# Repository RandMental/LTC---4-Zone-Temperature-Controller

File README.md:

# Labfin Temperature Controller
* 4 indepenednt zones 
* Web server for OTA monitoring and customisation
* MQTT client for Home Assistant 
* SD card for config

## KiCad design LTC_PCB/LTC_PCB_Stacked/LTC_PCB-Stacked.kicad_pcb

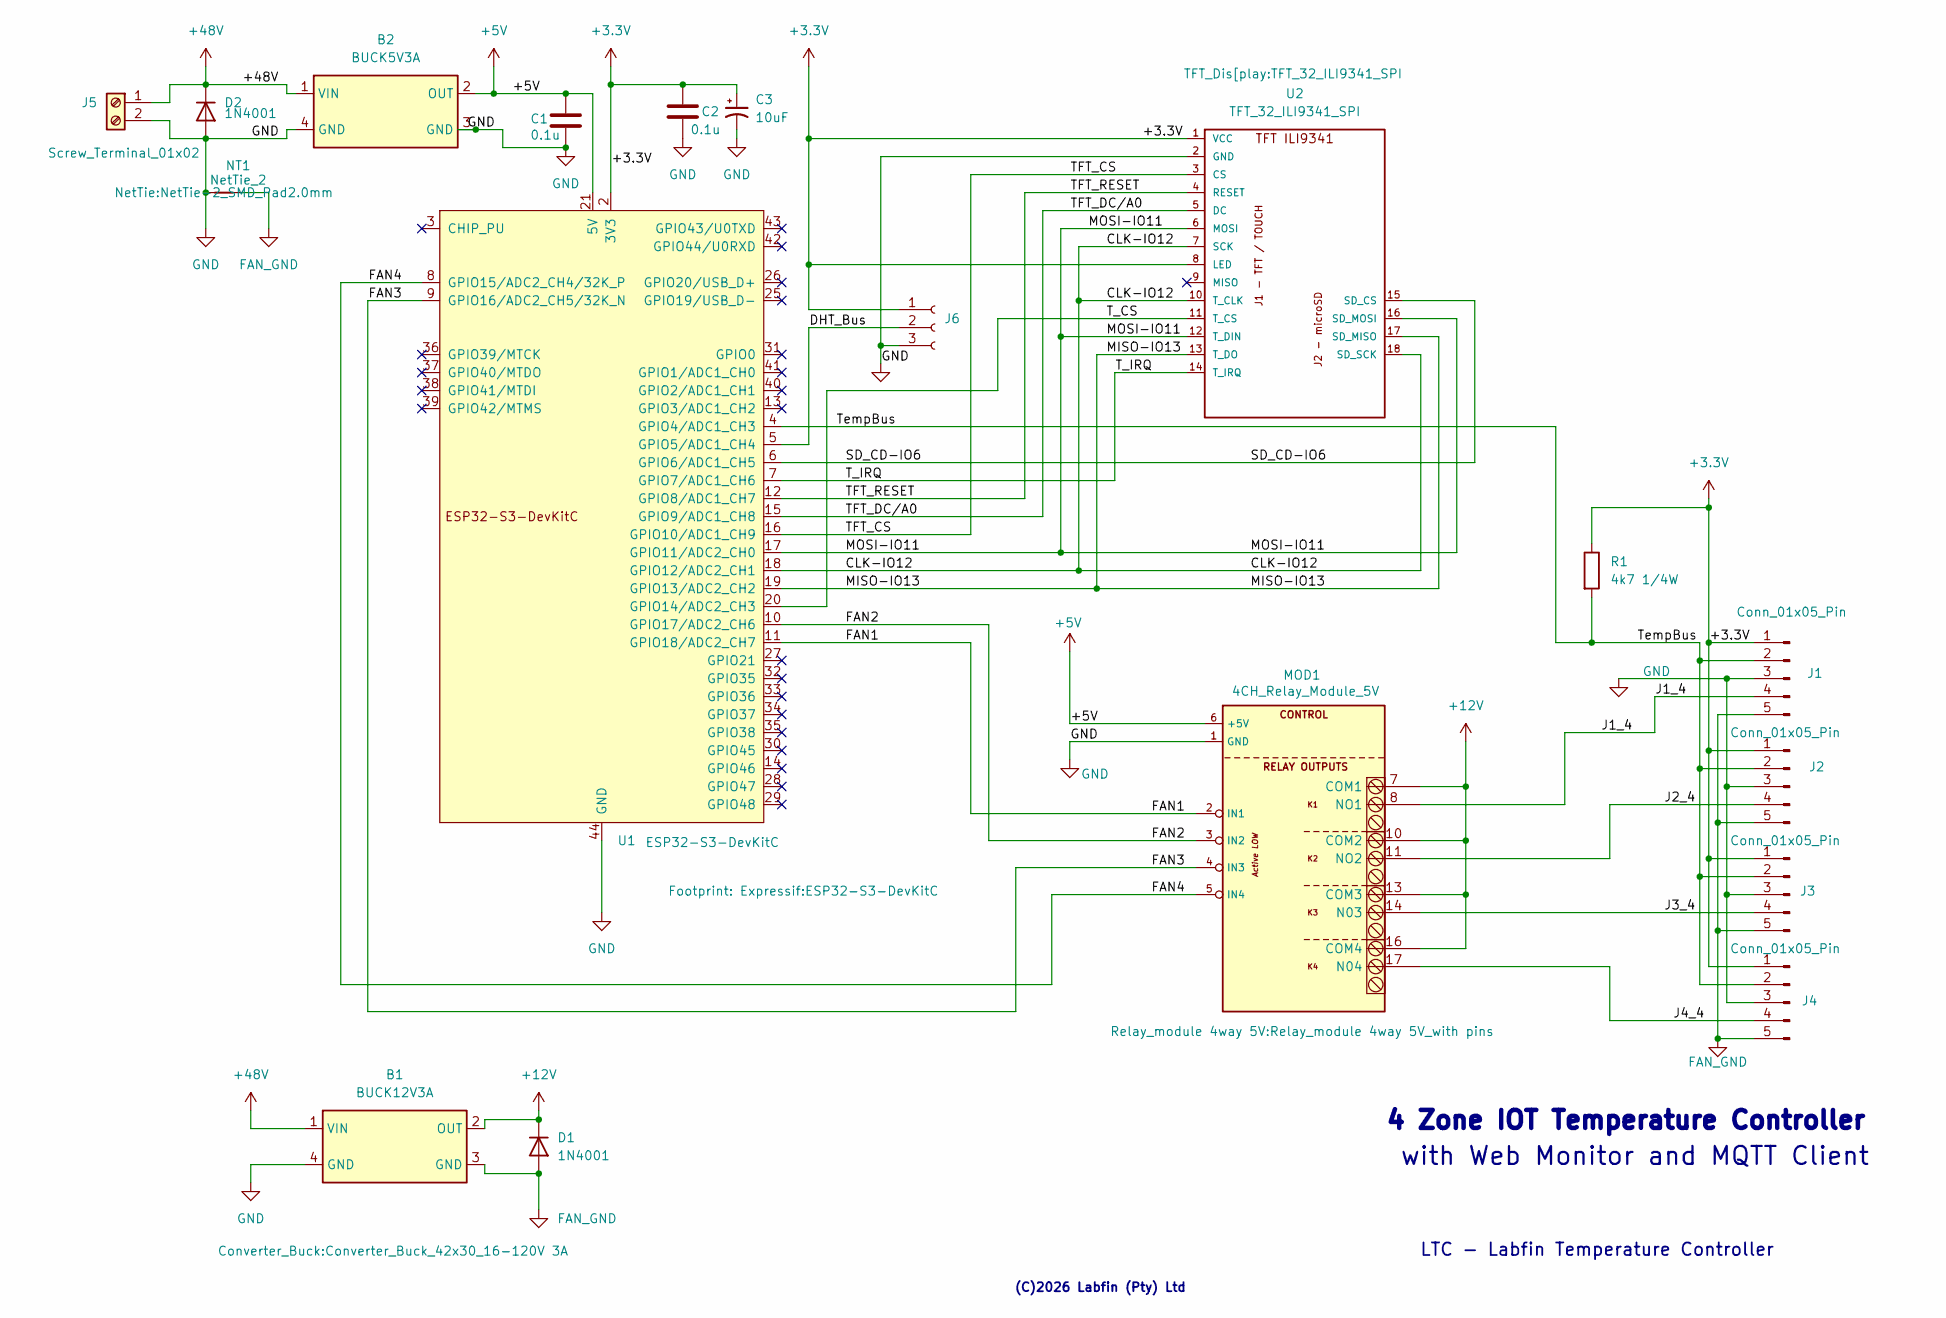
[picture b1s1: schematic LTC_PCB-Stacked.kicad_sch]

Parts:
B1: BUCK12V3A; Converter_Buck_42x30_16-120V 3A
B2: BUCK5V3A; Converter_Buck_42x30_16-120V 3A
C1, C2: 0.1u; C_Disc_D5.1mm_W3.2mm_P5.00mm
C3: 10uF; CP_Radial_D8.0mm_P5.00mm
D1, D2: 1N4001; D_DO-41_SOD81_P10.16mm_Horizontal
J1, J2, J3, J4: Conn_01x05_Pin; Molex_SL_171971-0005_1x05_P2.54mm_Vertical
J5: Screw_Terminal_01x02; Molex_KK-254_AE-6410-02A_1x02_P2.54mm_Vertical
J6: Conn_01x03_Socket; Molex_KK-254_AE-6410-03A_1x03_P2.54mm_Vertical
MOD1: 4CH_Relay_Module_5V; Relay_module 4way 5V_with pins; MPN SRD-05VDC-SL-C
NT1: NetTie_2; NetTie-2_SMD_Pad2.0mm
R1: 4k7 1/4W; R_Axial_DIN0207_L6.3mm_D2.5mm_P15.24mm_Horizontal
U1: ESP32-S3-DevKitC
U2: TFT_32_ILI9341_SPI

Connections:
+3.3V: C2.1, C3.1, J1.1, J2.1, J3.1, J4.1, J6.1, R1.1, U1.1 (3V3), U1.2 (3V3), U2.1 (VCC), U2.8 (LED)
+5V: B2.2 (OUT), C1.1, MOD1.6 (+5V), U1.21 (5V)
+12V: B1.2 (OUT), D1.1 (K), MOD1.7 (COM1), MOD1.10 (COM2), MOD1.13 (COM3), MOD1.16 (COM4)
+48V: B1.1 (VIN), B2.1 (VIN), D2.1 (K), J5.1
/CLK-IO12: U1.18 (GPIO12/ADC2_CH1), U2.7 (SCK), U2.10 (T_CLK), U2.18 (SD_SCK)
/DHT_Bus: J6.2, U1.5 (GPIO5/ADC1_CH4)
/FAN1: MOD1.2 (IN1), U1.11 (GPIO18/ADC2_CH7)
/FAN2: MOD1.3 (IN2), U1.10 (GPIO17/ADC2_CH6)
/FAN3: MOD1.4 (IN3), U1.9 (GPIO16/ADC2_CH5/32K_N)
/FAN4: MOD1.5 (IN4), U1.8 (GPIO15/ADC2_CH4/32K_P)
/J1_4: J1.4, MOD1.8 (NO1)
/J2_4: J2.4, MOD1.11 (NO2)
/J3_4: J3.4, MOD1.14 (N03)
/J4_4: J4.4, MOD1.17 (N04)
/MISO-IO13: U1.19 (GPIO13/ADC2_CH2), U2.13 (T_DO), U2.17 (SD_MISO)
/MOSI-IO11: U1.17 (GPIO11/ADC2_CH0), U2.6 (MOSI), U2.12 (T_DIN), U2.16 (SD_MOSI)
/SD_CD-IO6: U1.6 (GPIO6/ADC1_CH5), U2.15 (SD_CS)
/TFT_CS: U1.16 (GPIO10/ADC1_CH9), U2.3 (CS)
/TFT_DC/A0: U1.15 (GPIO9/ADC1_CH8), U2.5 (DC)
/TFT_RESET: U1.12 (GPIO8/ADC1_CH7), U2.4 (RESET)
/T_CS: U1.20 (GPIO14/ADC2_CH3), U2.11 (T_CS)
/T_IRQ: U1.7 (GPIO7/ADC1_CH6), U2.14 (T_IRQ)
/TempBus: J1.2, J2.2, J3.2, J4.2, R1.2, U1.4 (GPIO4/ADC1_CH3)
FAN_GND: B1.3 (GND), D1.2 (A), J1.5, J2.5, J3.5, J4.5, NT1.2
GND: B1.4 (GND), B2.3 (GND), B2.4 (GND), C1.2, C2.2, C3.2, D2.2 (A), J1.3, J2.3, J3.3, J4.3, J5.2, J6.3, MOD1.1 (GND), NT1.1, U1.22 (GND), U1.23 (GND), U1.24 (GND), U1.44 (GND), U2.2 (GND)

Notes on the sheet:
(C)2026 Labfin (Pty) Ltd
LTC - Labfin Temperature Controller
4 Zone IOT Temperature Controller
with Web Monitor and MQTT Client

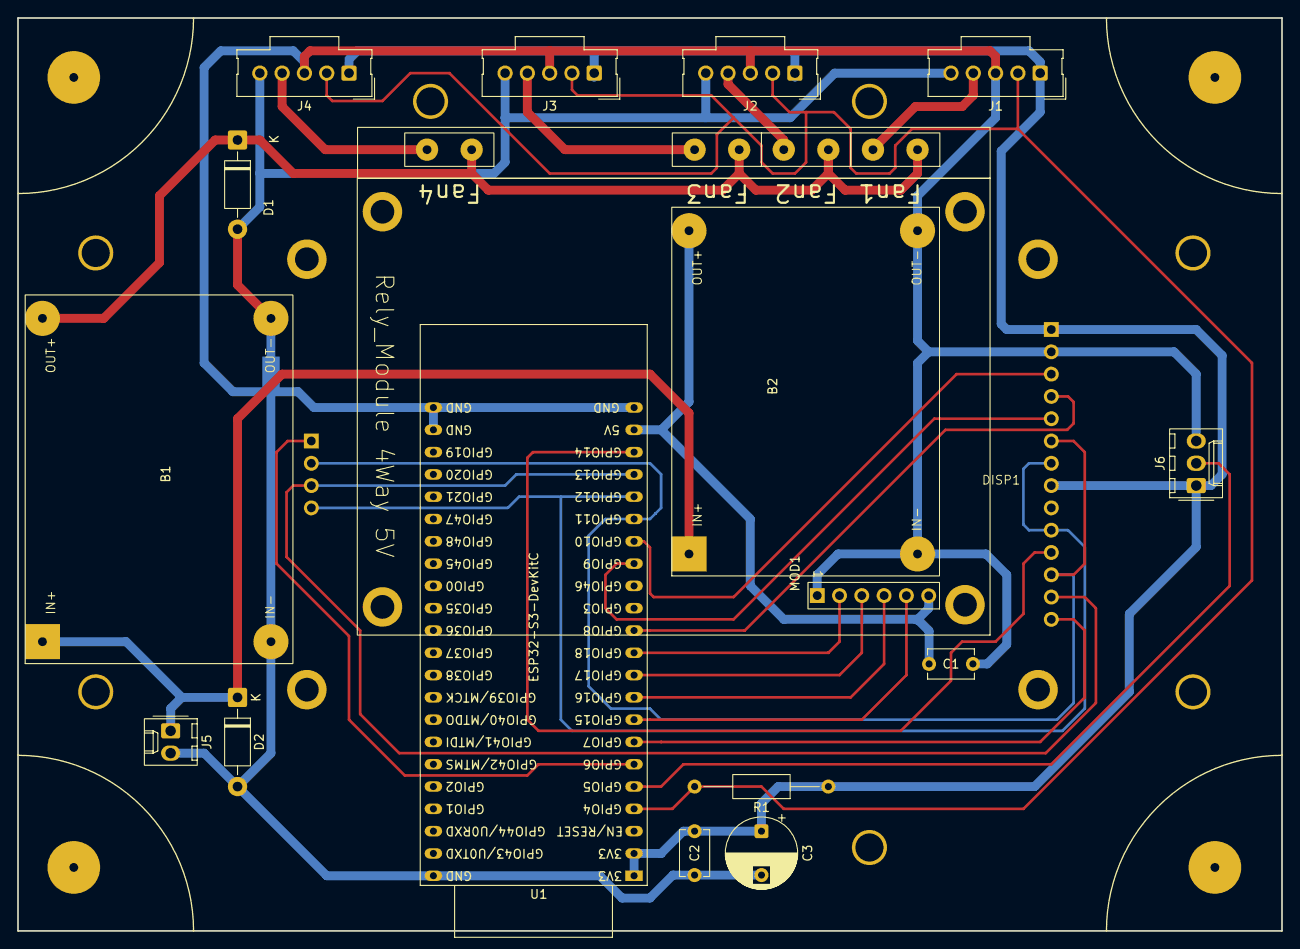
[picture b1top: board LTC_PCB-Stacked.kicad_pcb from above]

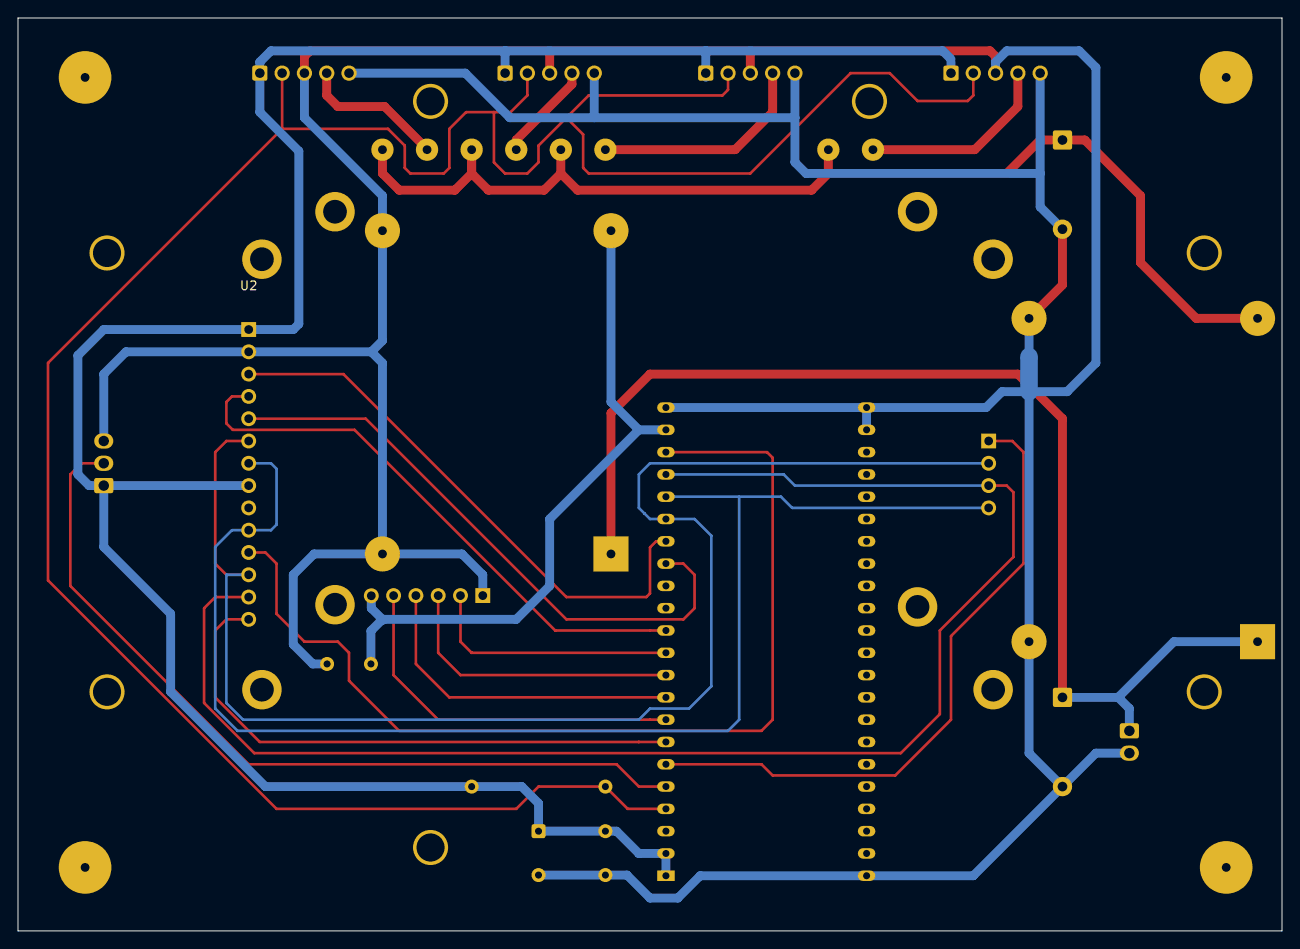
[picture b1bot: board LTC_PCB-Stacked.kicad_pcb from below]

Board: 2 copper layers, 144.0 x 104.0 mm, 19 parts (2 on the bottom side), 25 nets.

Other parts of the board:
DISP1: Hammond 1556EA; Hammond_1556EA

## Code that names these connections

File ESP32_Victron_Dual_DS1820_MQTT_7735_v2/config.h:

#pragma once`	0```	```````````````

/*
 * =============================================================================
 * config.h - Configuration file for Victron Temperature Monitor
 * =============================================================================
 *
 * Edit this file to configure WiFi, MQTT, pins, thresholds, and timing.
 * Keep sensitive credentials here and exclude from version control if needed.
 *
 * =============================================================================
 */

#ifndef CONFIG_H
#define CONFIG_H

// ================================ DEBUG CONFIGURATION ================================
// Debug levels: 0=none, 1=error, 2=warn, 3=info, 4=debug
#define DEBUG_LEVEL 3

// ================================ DEVICE CONFIGURATION ================================
#define NUM_TEMP_SENSORS  4   // Number of DS18B20 temperature sensors
#define NUM_FANS          4   // Number of fan relays

// ================================ WIFI CONFIG ================================
#define WIFI_SSID               "IOT"
#define WIFI_PASSWORD           "7z14kpak31631"
#define WIFI_CONNECT_TIMEOUT_MS 10000
#define WIFI_RECONNECT_INTERVAL_MS 30000

// ================================ MQTT CONFIG ================================
#define MQTT_HOST           "192.168.40.250"
#define MQTT_PORT           1883
#define MQTT_USER           "labmqtt"
#define MQTT_PASSW          "7Z14kp"
#define MQTT_CLIENT_NAME    "VictronTempMonitor"

// MQTT Base Topic
#define MQTT_BASE_TOPIC     "solar"

// MQTT Topics - Monitor Status
#define MQTT_PUB_STATUS     "solar/monitor/status"
#define MQTT_PUB_WIFI_RSSI  "solar/monitor/rssi"
#define MQTT_PUB_WIFI_IP    "solar/monitor/ip"
#define MQTT_PUB_UPTIME     "solar/monitor/uptime"
#define MQTT_PUB_HEAP_FREE  "solar/monitor/heap_free"
#define MQTT_PUB_VERSION    "solar/monitor/version"

// MQTT Topics - Ambient (DHT22)
#define MQTT_PUB_AMB_TEMP   "solar/ambient/temperature"
#define MQTT_PUB_AMB_HUM    "solar/ambient/humidity"

// MQTT QoS and retain settings
#define MQTT_QOS            1
#define MQTT_RETAIN         true

// ================================ NTP CONFIG ================================
#define NTP_SERVER          "192.168.20.1"
#define GMT_OFFSET_SEC      7200        // GMT+2 (South Africa)
#define DAYLIGHT_OFFSET_SEC 0           // No DST

// ================================ PIN DEFINITIONS 
/* Hardware Connections - ESP32-S3-DevKitC-1 (44-pin)
 *
 * ESP32-S3 GPIO Safety:
 *   - Strapping pins (avoid): GPIO 0, 3, 45, 46
 *   - USB pins (avoid): GPIO 19, 20
 *   - JTAG pins (avoid): GPIO 39-42
 *   - UART0 (avoid): GPIO 43, 44
 *   - PSRAM (if equipped, avoid): GPIO 26-32
 *   - Safe GPIOs: 1-18, 21, 35-38, 47-48
 */

// Sensor pins
#define ONEWIRE_PIN         4     // DS18B20 bus (with 4.7k pull-up to 3.3V)
#define DHTPIN              5     // DHT22 (with 10k pull-up to 3.3V)

//  ================================
// ILI9342 3.2" (240x320) Display
#define TFT_WIDTH     240
#define TFT_HEIGHT    320
#define TFT_ROTATION  2   // Portrait, USB at bottom

// TFT Display pins (SPI2)
#define TFT_CS              10    // SPI2 default SS
#define TFT_DC              9
#define TFT_RST             8
#define TFT_MOSI            11    // SPI2 default MOSI
#define TFT_SCLK            12    // SPI2 default SCK
#define TFT_MISO            13    // SPI2 default MISO (not used by display)


// XPT2046 Touchscreen pin connections (shares SPI2 bus with display)
// T_CLK  -> GPIO12 (SPI2 SCK, shared with TFT)0...
// T_DIN  -> GPIO11 (SPI2 MOSI, shared with TFT)
// T_DO   -> GPIO13 (SPI2 MISO, required for touch readback)
#define TCH_CS              14    // Dedicated Touch CS (active low)
#define TCH_IRQ             7     // Touch interrupt (low when touched)

// SD Card (shares SPI2 bus with display and touchscreen)
#define SD_CS_PIN           6     // SD card chip select (active low)

// RGB LED (WS2812 NeoPixel on ESP32-S3-DevKitC-1)
#define RGB_LED_PIN         48    // Onboard RGB LED
#define RGB_BRIGHTNESS      25    // LED brightness (0-255), keep low to avoid glare
#define RGB_PULSE_MS        100   // How long the LED stays on during pulse

// Fan relay pins
// FAN_ACTIVE_LOW: true = LOW turns fan ON (inverted), false = HIGH turns fan ON (normal)
#define FAN_ACTIVE_LOW      true
// Unused sensors (no valid address) keep fan off
// Sensor errors on configured sensors force fan ON for safety
#define FAN_RELAY_0         15    // MPPT_W
#define FAN_RELAY_1         16    // MPPT_E
#define FAN_RELAY_2         17    // MultiPlus1
#define FAN_RELAY_3         18    // Batteries

// ================================ BUTTON TIMING ================================
#define BUTTON_DEBOUNCE_MS      100     // Minimum press to count as valid
#define SHORT_PRESS_MAX_MS      1000    // Under 1s = test fans or skip
#define SKIP_PRESS_MIN_MS       1000    // 1s+ in assignment mode = skip
#define LONG_PRESS_MS           5000    // 5+ seconds = enter assignment mode
#define TEST_FAN_DURATION_MS    5000    // How long fans run during test
#define ASSIGNMENT_TIMEOUT_MS   30000   // 30s timeout per step (reboot if no sensor)
#define CONFIRM_PRESS_MIN_MS    200     // Minimum button press for confirmation
#define CONFIRM_RELEASE_DELAY_MS 1000   // Wait 1s after button release before advancing
#define STARTUP_SCREEN_MS       500     // Brief startup display

// ================================ TEMPERATURE THRESHOLDS ================================
// Per-device thresholds: { MPPT_W, MPPT_E, MultiPlus_1, Batteries }
#define TEMP_FAN_OFF_MPPT_W     35.0f
#define TEMP_FAN_OFF_MPPT_E     35.0f
#define TEMP_FAN_OFF_MULTIPLUS  35.0f
#define TEMP_FAN_OFF_BATTERIES  30.0f

#define TEMP_FAN_ON_MPPT_W      35.0f
#define TEMP_FAN_ON_MPPT_E      35.0f
#define TEMP_FAN_ON_MULTIPLUS   35.0f
#define TEMP_FAN_ON_BATTERIES   30.0f

#define TEMP_FAN_HYSTERESIS     5.0f    // Turn off fan when temp drops this much below FAN_ON
#define TEMP_MIN_VALID          -5.0f   // Minimum valid DS18B20 reading
#define TEMP_MAX_VALID          75.0f   // Maximum valid DS18B20 reading

// ================================ TIMING INTERVALS ================================
#define SENSOR_INTERVAL     2000    // 2s - read sensors
#define DISP_INTERVAL       4000    // 4s - cycle display screens
#define MQTT_INTERVAL       30000   // 30s - publish sensor readings
#define STATUS_INTERVAL     60000   // 1min - publish status/heap
#define NTP_INTERVAL        7200000 // 2h - sync NTP time
#define WDT_TIMEOUT_S       60      // Watchdog timeout (seconds)

// ================================ SENSOR FILTERING ================================
#define FILTER_SAMPLES          5   // Moving average window size
#define SENSOR_ERROR_THRESHOLD  3   // Consecutive errors before marking sensor failed

// ================================ STARTUP SCREEN ================================
// Startup screen title (3 lines, centered)
#define STARTUP_LINE_1      "Labfin"
#define STARTUP_LINE_2      "Temperature"
#define STARTUP_LINE_3      "Controller"

// ================================ DEVICE NAMES ================================
// Device names for display (max 10 chars)
#define DEVICE_NAME_0       "MPPT_Wes"
#define DEVICE_NAME_1       "MPPT_Oos"
#define DEVICE_NAME_2       "Inverter"
#define DEVICE_NAME_3       "Batterye"

// MQTT topic suffixes for each device
#define DEVICE_TOPIC_0      "mppt_w"
#define DEVICE_TOPIC_1      "mppt_e"
#define DEVICE_TOPIC_2      "inverter"
#define DEVICE_TOPIC_3      "batteries"



// ================================ DS18B20 SENSOR ADDRESSES ================================
// 1-Wire addresses for each temperature sensor (8 bytes each)
// Use sensor assignment mode (long press button >5s) to discover addresses
// Addresses starting with 0x28,0x00,0x00 are placeholders (sensor not configured)
//
// After assignment, addresses are printed to Serial in this format - copy them here:
#define SENSOR_ADDR_0  { 0x28, 0xD6, 0x0D, 0x95, 0xF0, 0x01, 0x3C, 0xB0 }  
#define SENSOR_ADDR_1  { 0x28, 0x79, 0xEC, 0x95, 0xF0, 0xFF, 0x3C, 0x9A }  
#define SENSOR_ADDR_2  { 0x28, 0x00, 0x00, 0x00, 0x00, 0x00, 0x00, 0x00 }  
#define SENSOR_ADDR_3  { 0x28, 0x00, 0x00, 0x00, 0x00, 0x00, 0x00, 0x00 }  

// ======================================================
// Fixed layout values for 240x320 display
// ======================================================
#define TITLE_Y           12
#define CONTENT_Y         48
#define LINE_SPACING      30
#define WIFI_ICON_SCALE   2
#define STATUS_ICON_SCALE 2

#endif // CONFIG_H

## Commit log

2026-02-23 LTC Version 2.2.2
2026-02-23 Change headings to bullet points in README
2026-02-23 Add PCB and Bezels
    ADd PCB version 1 as ordered
